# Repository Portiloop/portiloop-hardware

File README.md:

# Portiloop hardware

This repository documents hardware implementations of the `Portiloop` device. 
Which is a portable EEG closed-loop stimulation device.
[The software repository](https://github.com/Portiloop/portiloop-software) enables controlling the device from a simple Graphical User Interface (GUI).

The last hardware iteration of the `Portiloop` device consists of a PCB built around an [ADS1299 chip](https://www.ti.com/product/ADS1299) 
with connectors for a [Coral Dev Board Mini](https://coral.ai/products/dev-board-mini/#documentation).
The `ADS1299` is an ADC responsible for processing analog EEG signal.

This repository open-sources all relevant plans for building this implementation.

To view the full interactive 3D model, click below:

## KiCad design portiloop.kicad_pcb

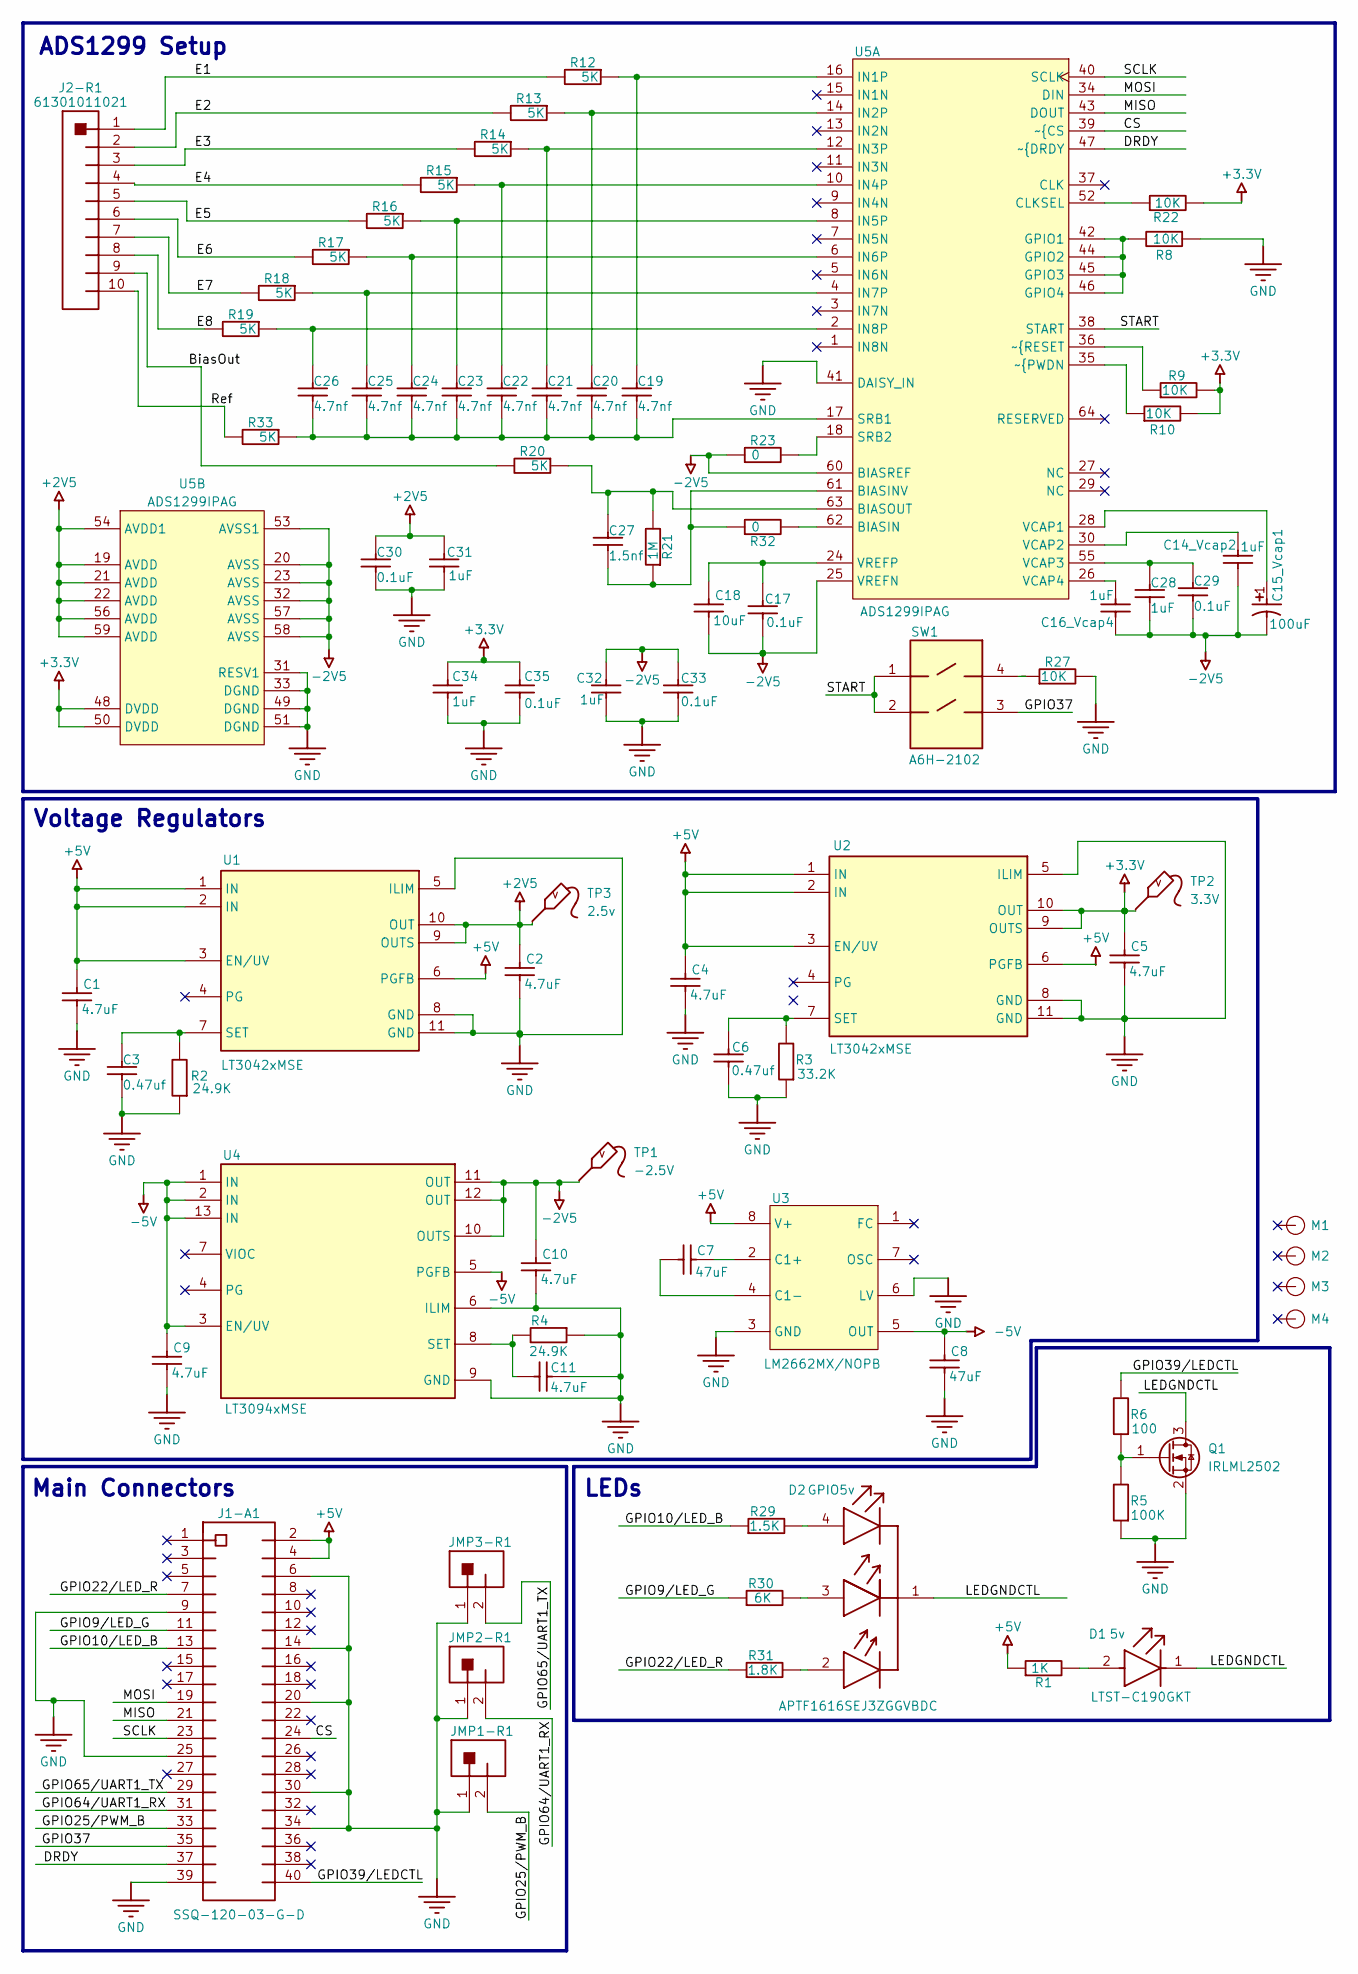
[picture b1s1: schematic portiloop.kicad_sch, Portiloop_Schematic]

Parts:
C1, C2, C4, C5, C9, C10, C11: 4.7uF; 3216[1206]_cap_3d
C3, C6: 0.47uf; 1608[0603]_cap_3d
C7, C8: 47uF; 3216[1206]_cap_3d
C14_Vcap2, C16_Vcap4, C28, C31, C32, C34: 1uF; 1608[0603]_cap_3d
C15_Vcap1: 100uF; KEMT-T491-D_M
C17, C29, C30, C33, C35: 0.1uF; 1608[0603]_cap_3d
C18: 10uF; 3216[1206]_cap_3d
C19, C20, C21, C22, C23, C24, C25, C26: 4.7nf; 1608[0603]_cap_3d
C27: 1.5nf; 1608[0603]_cap_3d
D1: LTST-C190GKT; FP-LTST-C190GKT-MFG
D2: APTF1616SEJ3ZGGVBDC; FP-APTF1616SEJ3ZGGVBDC-MFG
J1-A1: SSQ-120-03-G-D; FP-SSQ-120-03-G-D-MFG
J2-R1: 61301011021
JMP1-R1, JMP2-R1, JMP3-R1: 61300211021
M1, M2, M3, M4: board_screw
Q1: IRLML2502; SOT-23
R1: 1K; 1608[0603]_res_3d
R2, R4: 24.9K; 1608[0603]_res_3d
R3: 33.2K; 1608[0603]_res_3d
R5: 100K; 1608[0603]_res_3d
R6: 100; 1608[0603]_res_3d
R8, R22: 10k; 1608[0603]_res_3d
R9, R10, R27: 10K; 1608[0603]_res_3d
R12, R13, R14, R15, R16, R17, R18, R19, R20, R33: 5k; 1608[0603]_res_3d
R21: 1M; 1608[0603]_res_3d
R23, R32: 0; 1608[0603]_res_3d
R29: 1.5K; 1608[0603]_res_3d
R30: 6K; 1608[0603]_res_3d
R31: 1.8K; 1608[0603]_res_3d
SW1: A6H-2102; FP-A6H-2102-MFG
TP1: -2.5V; TESTPOINT
TP2: 3.3V; TESTPOINT
TP3: 2.5v; TESTPOINT
U1, U2: LT3042xMSE; FP-MSE-10-05-08-1664-IPC_C
U3: LM2662MX/NOPB; D0008A_M
U4: LT3094xMSE; FP-MSE-12-05-08-1666-IPC_A
U5: ADS1299IPAG; PAG0064A_M

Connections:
+2V5: C2.2, C30.2, C31.2, TP3.1 (T), U1.9 (OUTS), U1.10 (OUT), U5.19 (AVDD), U5.21 (AVDD), U5.22 (AVDD), U5.54 (AVDD1), U5.56 (AVDD), U5.59 (AVDD)
+3.3V: C5.2, C34.2, C35.2, R9.1, R10.1, R22.1, TP2.1 (T), U2.9 (OUTS), U2.10 (OUT), U5.48 (DVDD), U5.50 (DVDD)
+5V: C1.2, C4.2, J1-A1.2, J1-A1.4, R1.2, U1.1 (IN), U1.2 (IN), U1.3 (EN/UV), U1.6 (PGFB), U2.1 (IN), U2.2 (IN), U2.3 (EN/UV), U2.6 (PGFB), U3.8 (V+)
-2V5: C10.2, C14_Vcap2.1, C15_Vcap1.2, C16_Vcap4.1, C17.2, C18.1, C28.1, C29.1, C32.2, C33.2, R23.2, TP1.1 (T), U4.10 (OUTS), U4.11 (OUT), U4.12 (OUT), U5.20 (AVSS), U5.23 (AVSS), U5.25 (VREFN), U5.32 (AVSS), U5.53 (AVSS1), U5.57 (AVSS), U5.58 (AVSS), U5.60 (BIASREF)
-5V: C8.2, C9.2, U3.5 (OUT), U4.1 (IN), U4.2 (IN), U4.3 (EN/UV), U4.5 (PGFB), U4.13 (IN)
/BiasOut: J2-R1.9, R20.1
/CS: J1-A1.24, U5.39 (~{CS)
/DRDY: J1-A1.37, U5.47 (~{DRDY)
/E1: J2-R1.1, R12.1
/E2: J2-R1.2, R13.1
/E3: J2-R1.3, R14.1
/E4: J2-R1.4, R15.1
/E5: J2-R1.5, R16.1
/E6: J2-R1.6, R17.1
/E7: J2-R1.7, R18.1
/E8: J2-R1.8, R19.1
/GPIO9/LED_G: J1-A1.11, R30.2
/GPIO10/LED_B: J1-A1.13, R29.2
/GPIO22/LED_R: J1-A1.7, R31.2
/GPIO25/PWM_B: J1-A1.33, JMP1-R1.2
/GPIO37: J1-A1.35, SW1.3
/GPIO39/LEDCTL: J1-A1.40, R6.1
/GPIO64/UART1_RX: J1-A1.31, JMP2-R1.2
/GPIO65/UART1_TX: J1-A1.29, JMP3-R1.2
/LEDGNDCTL: D1.1 (C), D2.1 (COMMON_CATHODE), Q1.3 (D)
/MISO: J1-A1.21, U5.43 (DOUT)
/MOSI: J1-A1.19, U5.34 (DIN)
/Ref: J2-R1.10, R33.1
/SCLK: J1-A1.23, U5.40 (SCLK)
/START: SW1.1, SW1.2, U5.38 (START)
GND: C1.1, C2.1, C3.1, C4.1, C5.1, C6.2, C8.1, C9.1, C10.1, C11.1, C30.1, C31.1, C32.1, C33.1, C34.1, C35.1, J1-A1.6, J1-A1.9, J1-A1.14, J1-A1.20, J1-A1.25, J1-A1.30, J1-A1.34, J1-A1.39, JMP1-R1.1, JMP2-R1.1, JMP3-R1.1, Q1.2 (S), R2.2, R3.2, R4.2, R5.2, R8.2, R27.1, U1.5 (ILIM), U1.8 (GND), U1.11 (GND), U2.5 (ILIM), U2.8 (GND), U2.11 (GND), U3.3 (GND), U3.6 (LV), U4.6 (ILIM), U4.9 (GND), U5.31 (RESV1), U5.33 (DGND), U5.41 (DAISY_IN), U5.49 (DGND), U5.51 (DGND)
unnamed: D1.2 (A), R1.1
unnamed: D2.4 (BLUE_A), R29.1
unnamed: D2.3 (GREEN_A), R30.1
unnamed: D2.2 (RED_A), R31.1
unnamed: Q1.1 (G), R5.1, R6.2
unnamed: R27.2, SW1.4
unnamed: C3.2, R2.1, U1.7 (SET)
unnamed: C6.1, R3.1, U2.7 (SET)
unnamed: C7.2, U3.2 (C1+)
unnamed: C7.1, U3.4 (C1-)
unnamed: C11.2, R4.1, U4.8 (SET)
unnamed: R32.1, U5.62 (BIASIN)
unnamed: C27.1, R21.2, R32.2, U5.61 (BIASINV)
unnamed: C27.2, R20.2, R21.1, U5.63 (BIASOUT)
unnamed: R22.2, U5.52 (CLKSEL)
unnamed: R8.1, U5.42 (GPIO1), U5.44 (GPIO2), U5.45 (GPIO3), U5.46 (GPIO4)
unnamed: C19.2, R12.2, U5.16 (IN1P)
unnamed: C20.2, R13.2, U5.14 (IN2P)
unnamed: C21.2, R14.2, U5.12 (IN3P)
unnamed: C22.2, R15.2, U5.10 (IN4P)
unnamed: C23.2, R16.2, U5.8 (IN5P)
unnamed: C24.2, R17.2, U5.6 (IN6P)
unnamed: C25.2, R18.2, U5.4 (IN7P)
unnamed: C26.2, R19.2, U5.2 (IN8P)
unnamed: C19.1, C20.1, C21.1, C22.1, C23.1, C24.1, C25.1, C26.1, R33.2, U5.17 (SRB1)
unnamed: R23.1, U5.18 (SRB2)
unnamed: C15_Vcap1.1, U5.28 (VCAP1)
unnamed: C14_Vcap2.2, U5.30 (VCAP2)
unnamed: C28.2, C29.2, U5.55 (VCAP3)
unnamed: C16_Vcap4.2, U5.26 (VCAP4)
unnamed: C17.1, C18.2, U5.24 (VREFP)
unnamed: R10.2, U5.35 (~{PWDN)
unnamed: R9.2, U5.36 (~{RESET)

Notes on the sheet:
Voltage Regulators
ADS1299 Setup
LEDs
Main Connectors

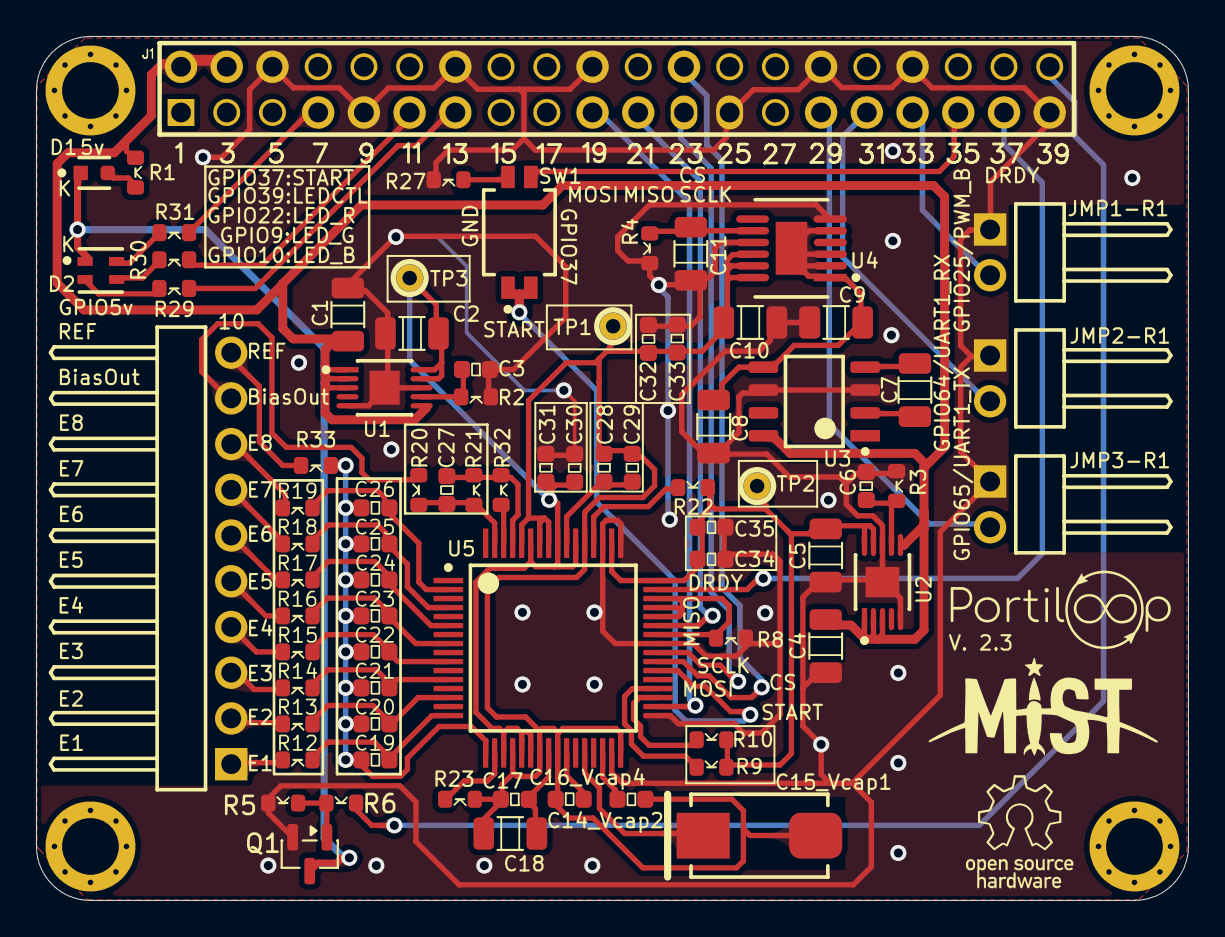
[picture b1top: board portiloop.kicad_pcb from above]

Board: 2 copper layers, 64.0 x 48.0 mm, 81 parts (1 on the bottom side), 64 nets.

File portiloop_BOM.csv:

Id,Designator,Footprint,Quantity,Designation,Part #
1,"C10,C1,C5,C4,C2,C9,C11",3216[1206]_cap,7,4.7uF,CL31B475KBHNNNE
2,C15_Vcap1,KEMT-T491-D_M,1,100uF,T491D107K016AT
3,"C16_Vcap4,C34,C31,C14_Vcap2,C32,C28",1608[0603]_cap,6,1uF,CC0603KRX5R8BB105
4,C18,3216[1206]_cap,1,10uF,CC1206KKX7R8BB106
5,"C21,C26,C22,C20,C23,C19,C25,C24",1608[0603]_cap,8,4.7nf,CC0603KRX7R9BB472
6,C27,1608[0603]_cap,1,1.5nf,CC0603KRX7R9BB152
7,"C35,C17,C33,C29,C30",1608[0603]_cap,5,0.1uF,CC0603KRX7R9BB104
8,"C6,C3",1608[0603]_cap,2,0.47uf,CC0603KRX7R9BB474
9,"C8,C7",3216[1206]_cap,2,47uF,GRM31CR60J476ME19L
10,D2,FP-APTF1616SEJ3ZGGVBDC-MFG,1,APTF1616SEJ3ZGGVBDC,
11,D1,FP-LTST-C190GKT-MFG,1,LTST-C190GKT,
12,J1-A1,FP-SSQ-120-03-G-D-MFG,1,SSQ-120-03-G-D,
13,J2-R1,61301011021,1,61301011021,
14,"JMP1-R1,JMP2-R1,JMP3-R1",61300211021,3,61300211021,
15,"M2,M4,M3,M1",board_screw,4,DNP,DNP
16,Q1,SOT-23,1,IRLML2502,IRLML2502TRPBF
17,R1,1608[0603]_res,1,1K,RC0603FR-071KL
18,"R12,R19,R33,R14,R18,R20,R16,R17,R15,R13",1608[0603]_res,10,5K OR 4.99K,RC0603FR-074K99L
19,R21,1608[0603]_res,1,1M,RC0603FR-071ML
20,R29,1608[0603]_res,1,1.5K,RC0603FR-071K5L
21,R3,1608[0603]_res,1,33.2K,RC0603FR-0733K2L
22,R30,1608[0603]_res,1,6K OR 6.04K,RC0603FR-076K04L
23,R31,1608[0603]_res,1,1.8K,RC0603FR-071K8L
24,"R32,R23",1608[0603]_res,2,0,RC0603FR-070RL
25,"R4,R2",1608[0603]_res,2,24.9K,RC0603FR-0724K9L
26,R5,1608[0603]_res,1,100K,0603SAJ0104T5E
27,R6,1608[0603]_res,1,100,RC0603JR-07100RL
28,"R8,R9,R10,R22,R27",1608[0603]_res,5,10K,RC0603FR-0710KL
29,SW1,FP-A6H-2102-MFG,1,A6H-2102,
30,"TP1,TP2,TP3",TESTPOINT,1,DNP,DNP
31,"U2,U1",FP-MSE-10-05-08-1664-IPC_C,2,LT3042xMSE,LT3042EMSE#PBF
32,U3,D0008A_M,1,LM2662MX/NOPB,LM2662MX/NOPB
33,U4,FP-MSE-12-05-08-1666-IPC_A,1,LT3094xMSE,LT3094EMSE#PBF
34,U5,PAG0064A_M,1,ADS1299IPAG,

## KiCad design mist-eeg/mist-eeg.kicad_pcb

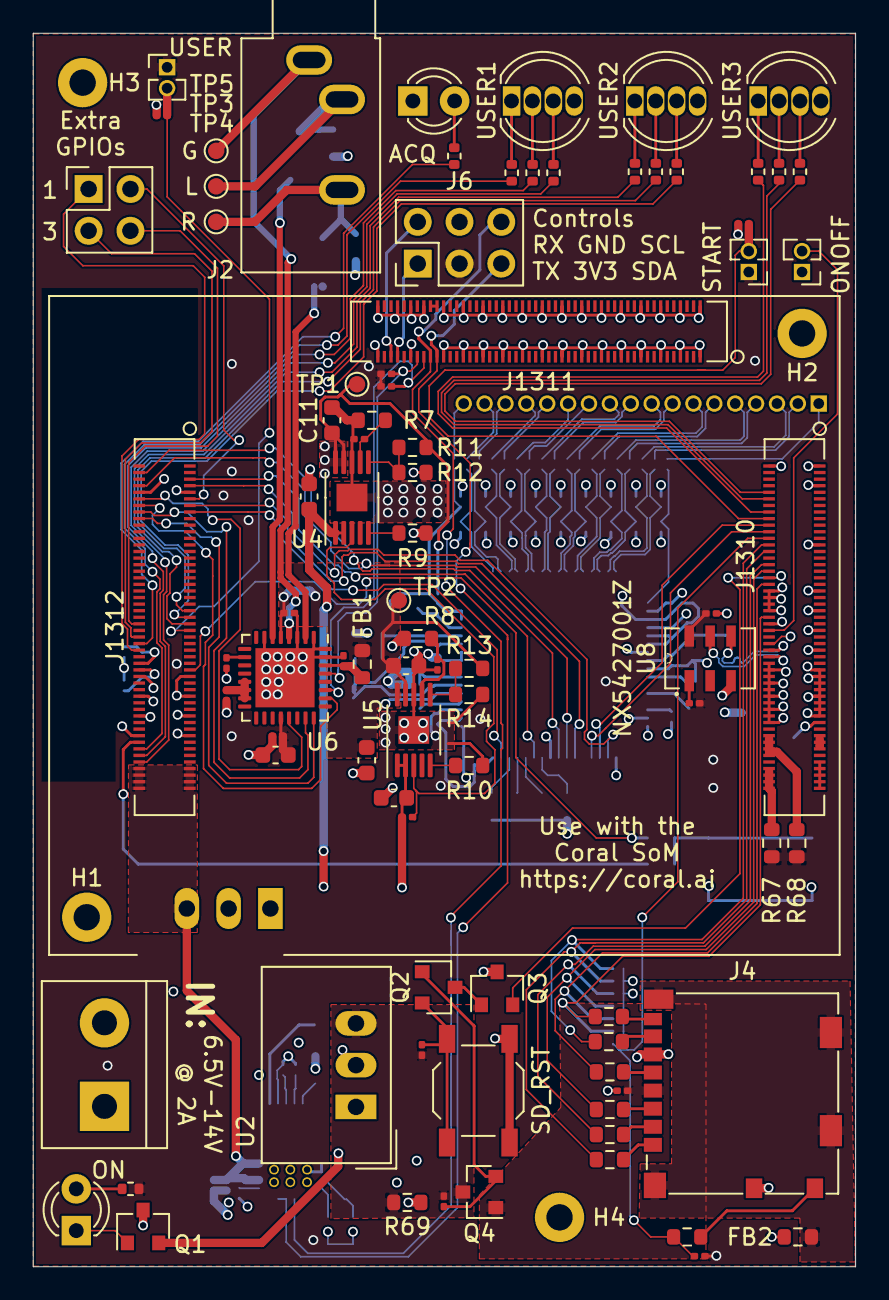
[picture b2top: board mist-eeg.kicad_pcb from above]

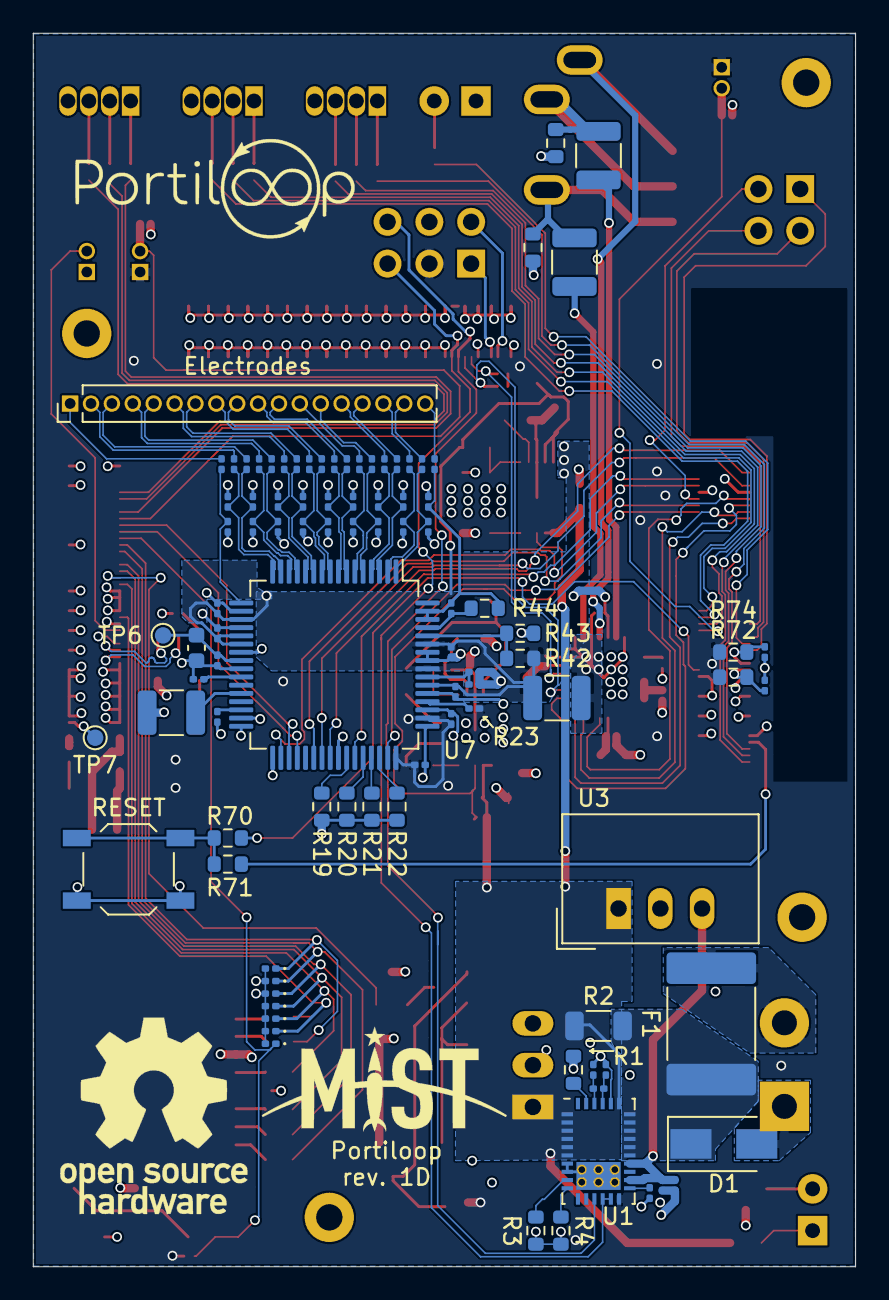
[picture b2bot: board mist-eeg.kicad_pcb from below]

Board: 4 copper layers, 50.0 x 75.0 mm, 185 parts (95 on the bottom side), 159 nets.

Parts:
C1, C2, C3, C4, C27, C28, C29, C32: 1uF; C_0201_0603Metric
C5, C6, C9, C10, C15, C16, C17, C20, C21, C22, C23, C24, C25, C30, C31, C53, C55, C56: 0u1F; C_0201_0603Metric
C7, C8, C11, C12, C18, C19, C54: 10uF; C_0603_1608Metric
C13, C14: 220uF; C_1210_3225Metric
C26, C33: 100uF; C_1210_3225Metric
C34, C35, C36, C37, C38, C39, C40, C41, C42, C43, C44, C45, C46, C47, C48, C49, C50, C51: 4n7F; C_0201_0603Metric
C52: 1n5F; C_0201_0603Metric
D1: D_TVS; D_SMA
D2: ON; LED_D3.0mm
D3: ACQ; LED_D3.0mm
D4: USER1; LED_D5.0mm-4_RGB
D5: USER3; LED_D5.0mm-4_RGB
D6: USER2; LED_D5.0mm-4_RGB
D7, D8, D9, D10, D11, D12, D13: TPD1E6B06DPLR; D_0201_0603Metric
F1: 3 A, 20 V; Fuse_2920_7451Metric
FB1, FB2: Ferrite_Bead_Small; R_0603_1608Metric
H1, H2, H3, H4: MountingHole; MountingHole_1.6mm
J1: Power_6.5V-14V; TerminalBlock_bornier-2_P5.08mm
J2: Audio; Jack_3.5mm_CUI_SJ1-3533NG_Horizontal
J3: Electrodes; PinHeader_1x18_P1.27mm_Vertical
J4: Micro_SD_Card_Det; microSD_HC_Molex_104031-0811
J5: Extra GPIOs; PinHeader_2x02_P2.54mm_Vertical
J6: Digital buses; PinHeader_2x03_P2.54mm_Vertical
J7: J1312; DF40HC3.0-100DS-0.4V58
J8: J1311; DF40HC3.0-100DS-0.4V58
J9: J1310; DF40HC3.0-100DS-0.4V58
Q1: NMOS_DGS (3V3); SOT-23
Q2, Q3: NMOS_DGS (3.3V); SOT-23
Q4: PMOS_DGS (3.3V @ 1A); SOT-23
R1, R3, R4, R9, R10, R11, R13, R58, R59, R60, R61, R62, R63, R64, R67, R70: 0R; R_0603_1608Metric
R2: DNF; R_1206_3216Metric
R5, R17, R18, R23, R55, R56, R57, R65, R66, R73, R75, R76: 4k7; R_0201_0603Metric
R6, R45, R46, R47, R48, R49, R50, R51, R52, R53, R54: 1k; R_0402_1005Metric
R7: TNPW060349K9BEEA; R_0603_1608Metric
R8: TNPW060318K0BEEA; R_0603_1608Metric
R12, R14, R15, R16, R19, R20, R21, R22: 10k; R_0603_1608Metric
R24, R25, R26, R27, R28, R29, R30, R31, R32, R33, R34, R35, R36, R37, R38, R39, R40, R41: 4k99; R_0201_0603Metric
R42, R43, R68, R69, R71, R72, R74: DNF; R_0603_1608Metric
R44: 1M; R_0603_1608Metric
SW1: START; PinHeader_1x02_P1.27mm_Vertical
SW2: USER; PinHeader_1x02_P1.27mm_Vertical
SW3: SD_RST; SW_SPST_TL3342
SW4: RESET; SW_SPST_TL3342
SW5: ONOFF; PinHeader_1x02_P1.27mm_Vertical
TP1: +5V0_ANA; TestPoint_Pad_D1.0mm
TP2: +1V8_ANA; TestPoint_Pad_D1.0mm
TP3: T; TestPoint_Pad_D1.0mm
TP4: R; TestPoint_Pad_D1.0mm
TP5: S; TestPoint_Pad_D1.0mm
TP6: VREFP; TestPoint_Pad_D1.0mm
TP7: ~POR~; TestPoint_Pad_D1.0mm
U1: LTC2947
U2: TSR_1-2433; Converter_DCDC_TRACO_TSR-1_THT
U3: TSR_2-2450; Converter_DCDC_TRACO_TSR-1_THT
U4, U5: LT3042xMSE; MSOP-10-1EP_3x3mm_P0.5mm_EP1.68x1.88mm
U6: SGTL5000XNAA3; QFN-32-1EP_5x5mm_P0.5mm_EP3.6x3.6mm
U7: ADS1299; TQFP-64_10x10mm_P0.5mm
U8: NX5427001Z

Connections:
+3V3: C17.1, C18.1, C28.1, C30.1, C56.2, J6.3, R6.1, R17.1, R18.1, R23.2, R57.1, R67.2, R68.2, R69.2, R72.2, R74.2, R76.2, SW1.1, SW2.1, U1.16, U6.20, U7.48, U7.50, U8.6
/+1V8_ANA: C12.1, C19.1, C21.1, FB1.2, R13.1, TP2.1, U5.9, U5.10, U6.5
/+3V3_SD: Q4.3, R65.1, R66.1, R69.1, U2.3
/+5V0_ANA: C11.1, C22.1, C23.1, C24.1, C25.1, C26.1, R11.1, R42.1, TP1.1, U4.9, U4.10, U7.19, U7.21, U7.22, U7.54, U7.56, U7.59
/+5V_SOM: C1.1, C2.1, J7.93, J7.94, J7.95, J7.96, J7.97, J7.98, J7.99, J7.100, U1.18, U1.20, U3.3
/AQUISITION: J7.56, R45.2
/AUDIO_BCLK: J7.18, U6.24
/AUDIO_LRCLK: J7.16, U6.23
/AUDIO_MCLK: J7.12, U6.21
/AUDIO_SCL: J8.87, R17.2, U6.29
/AUDIO_SDA: J8.85, R18.2, U6.27
/AUDIO_SDATA: J7.14, U6.26
/CTRL_SCL: J6.6, J8.83, U1.13
/CTRL_SDA: J6.5, J8.81, U1.14, U1.15
/EEG/BIASIN: C35.1, C52.2, R25.1, R44.2, U7.62, U7.63
/EEG/BIASINV: C52.1, R44.1, U7.61
/EEG/BIASREF: R42.2, R43.1, U7.60
/EEG/BIAS_ELEC_O: J3.18, R25.2
/EEG/IN1N: C37.2, R27.1, U7.15
/EEG/IN1P: C36.1, R26.1, U7.16
/EEG/IN1_ON: J3.3, R27.2
/EEG/IN1_OP: J3.2, R26.2
/EEG/IN2N: C39.2, R29.1, U7.13
/EEG/IN2P: C38.1, R28.1, U7.14
/EEG/IN2_ON: J3.5, R29.2
/EEG/IN2_OP: J3.4, R28.2
/EEG/IN3N: C41.2, R31.1, U7.11
/EEG/IN3P: C40.1, R30.1, U7.12
/EEG/IN3_ON: J3.7, R31.2
/EEG/IN3_OP: J3.6, R30.2
/EEG/IN4N: C43.2, R33.1, U7.9
/EEG/IN4P: C42.1, R32.1, U7.10
/EEG/IN4_ON: J3.9, R33.2
/EEG/IN4_OP: J3.8, R32.2
/EEG/IN5N: C45.2, R35.1, U7.7
/EEG/IN5P: C44.1, R34.1, U7.8
/EEG/IN5_ON: J3.11, R35.2
/EEG/IN5_OP: J3.10, R34.2
/EEG/IN6N: C47.2, R37.1, U7.5
/EEG/IN6P: C46.1, R36.1, U7.6
/EEG/IN6_ON: J3.13, R37.2
/EEG/IN6_OP: J3.12, R36.2
/EEG/IN7N: C49.2, R39.1, U7.3
/EEG/IN7P: C48.1, R38.1, U7.4
/EEG/IN7_ON: J3.15, R39.2
/EEG/IN7_OP: J3.14, R38.2
/EEG/IN8N: C51.2, R41.1, U7.1
/EEG/IN8P: C50.1, R40.1, U7.2
/EEG/IN8_ON: J3.17, R41.2
/EEG/IN8_OP: J3.16, R40.2
/EEG/REF_ELEC: C34.1, R24.1, U7.17
/EEG/REF_ELEC_O: J3.1, R24.2
/EEG/VREFP: C53.1, C54.1, TP6.1, U7.24
/EEG_MISO: J7.5, U7.43
/EEG_MOSI: J7.7, U7.34
/EEG_SCK: J7.4, U7.40
/EEG_START: J7.13, U7.38
/SD_CLK: D12.1, J9.48, R63.2
/SD_CMD: D11.1, J9.26, R62.2
/SD_DAT0: D7.1, J9.28, R58.2
/SD_DAT1: D8.1, J9.32, R59.2
/SD_DAT2: D9.1, J9.34, R60.2
/SD_DAT3: D10.1, J9.38, R61.2
/SD_DATA/+PWR: C55.1, J4.4, Q4.1
/START: J9.18, R55.1, SW1.2
/SoM/BOOT_MODE0: J7.64, R72.1, R73.2
/SoM/BOOT_MODE1: J7.62, R74.1, R75.2
/SoM/CLK+: J9.58, U8.4
/SoM/CLK-: J9.60, U8.5
/SoM/DCDC_3V3: J9.84, J9.86, J9.88, J9.90, R68.1
/SoM/EXTRA_1: J5.1, J7.58
/SoM/EXTRA_2: J5.2, J7.11
/SoM/EXTRA_3: J5.3, J7.54
/SoM/EXTRA_4: J5.4, J7.50
/SoM/NVCC_ENET_2V5: J9.83, J9.85, J9.87
/SoM/ONOFF: J9.52, SW5.2
/SoM/RXD: J6.2, J8.95
/SoM/TXD: J6.1, J8.93
/SoM/USB1_VBUS: J8.82, J8.84
/SoM/VDDA_1V8: J9.91, J9.93, J9.95, J9.97, J9.99
/SoM/VDD_3V3: J9.94, J9.96, J9.98, J9.100, R67.1
/SoM/~POR~: J9.79, TP7.1
/SoM/~PWR_ON~: J7.86, R71.1
/SoM/~RESET~: J7.63, R70.1
/USER: J7.51, R56.1, SW2.2
/USER1_B: J7.92, R48.2
/USER1_G: J7.90, R47.2
/USER1_R: J7.88, R46.2
/USER2_B: J7.47, R54.2
/USER2_G: J7.45, R53.2
/USER2_R: J7.49, R52.2
/USER3_B: J9.10, R51.2
/USER3_G: J9.12, R50.2
/USER3_R: J9.16, R49.2
/audio/CM: C15.1, U6.13, U6.14, U6.15
/audio/DVDD: C20.1, FB1.1, U6.30
/audio/HPGND: J2.S, TP5.1, U6.4
/audio/LEFT: C13.1, U6.6
/audio/R: C14.2, J2.R, R16.1, TP4.1
/audio/RIGHT: C14.1, U6.2
/audio/T: C13.2, J2.T, R15.1, TP3.1
/power/+PWR: C7.1, C8.1, Q1.2, R2.1, R5.2, U1.1, U1.2, U1.3, U1.4, U1.5, U1.6, U1.27, U2.1, U3.1, U4.1, U4.2, U5.1, U5.2
/power/+PWR_IN: D1.1, F1.1, R2.2, U1.21, U1.22, U1.23, U1.24, U1.25, U1.26
/power/AD0: R3.1, U1.9
/power/AD1: R4.1, U1.10
/power/audio-power/ENA: R5.1, U4.3, U5.3
/power/audio-power/LIM_1V8: R10.1, U5.5
/power/audio-power/LIM_5V0: R9.1, U4.5
/power/audio-power/PGFB_1V8: R13.2, R14.1, U5.6
/power/audio-power/PGFB_5V0: R11.2, R12.1, U4.6
/power/audio-power/SET_1V8: C10.1, R8.1, U5.7
/power/audio-power/SET_5V0: C9.1, R7.1, U4.7
/~EEG_CS~: J7.8, U7.39
/~EEG_DRDY~: J7.15, U7.47
/~EEG_PWDN~: J9.20, U7.35
/~EEG_RESET~: J9.22, U7.36
/~SD_CONNECTED~: D13.1, J9.24, R57.2, R64.2
/~SD_RST~: J9.36, Q3.2
GND: C1.2, C2.2, C3.1, C5.1, C6.1, C7.2, C8.2, C9.2, C10.2, C11.2, C12.2, C15.2, C16.2, C17.2, C18.2, C19.2, C20.2, C21.2, C22.2, C23.2, C24.2, C25.2, C26.2, C27.1, C28.2, C29.1, C30.2, C31.1, C32.1, C33.1, C34.2, C35.2, C36.2, C37.1, C38.2, C39.1, C40.2, C41.1, C42.2, C43.1, C44.2, C45.1, C46.2, C47.1, C48.2, C49.1, C50.2, C51.1, C53.2, C54.2, C55.2, C56.1, D1.2, D3.1, D4.4, D5.4, D6.4, D7.2, D8.2, D9.2, D10.2, D11.2, D12.2, D13.2, FB2.1, J1.1, J4.6, J4.9, J6.4, J7.9, J7.10, J7.65, J7.66, J7.71, J7.72, J7.77, J7.78, J7.83, J7.84, J8.1, J8.2, J8.7, J8.8, J8.13, J8.14, J8.19, J8.20, J8.25, J8.26, J8.31, J8.32, J8.37, J8.38, J8.43, J8.44, J8.49, J8.50, J8.55, J8.56, J8.61, J8.62, J8.67, J8.68, J8.73, J8.74, J8.79, J8.80, J8.86, J8.89, J8.90, J8.94, J8.99, J8.100, J9.1, J9.2, J9.7, J9.25, J9.39, J9.40, J9.42, J9.44, J9.45, J9.46, J9.50, J9.51, J9.56, J9.57, J9.62, J9.63, J9.64, J9.65, J9.66, J9.67, J9.68, J9.69, J9.70, J9.71, J9.72, J9.73, J9.74, J9.75, J9.76, J9.77, J9.78, J9.80, Q1.3, Q3.3, R1.2, R3.2, R4.2, R7.2, R8.2, R9.2, R10.2, R12.2, R14.2, R15.2, R16.2, R19.1, R20.1, R21.1, R22.1, R43.2, R55.2, R56.2, R73.1, R75.1, SW3.1, SW4.1, SW5.1, U1.7, U1.8, U1.28, U1.33, U2.2, U3.2, U4.8, U4.11, U5.8, U5.11, U6.1, U6.3, U6.7, U6.31, U6.32, U6.33, U7.18, U7.20, U7.23, U7.25, U7.31, U7.32, U7.33, U7.41, U7.49, U7.51, U7.53, U7.57, U7.58, U8.3
unnamed: C3.2, U1.17
unnamed: C4.1, C5.2, U1.29
unnamed: C4.2, C6.2, U1.30
unnamed: C16.1, U6.10
unnamed: C27.2, U7.26
unnamed: C29.2, C31.2, U7.55
unnamed: C32.2, U7.30
unnamed: C33.2, U7.28
unnamed: D2.1, Q1.1
unnamed: D2.2, R6.2
unnamed: D3.2, R45.1
unnamed: D4.1, R46.1
unnamed: D4.2, R47.1
unnamed: D4.3, R48.1
unnamed: D5.1, R49.1
unnamed: D5.2, R50.1
unnamed: D5.3, R51.1
unnamed: D6.1, R52.1
unnamed: D6.2, R53.1
unnamed: D6.3, R54.1
unnamed: F1.2, J1.2
unnamed: FB2.2, J4.11
unnamed: J4.1, R58.1
unnamed: J4.2, R59.1
unnamed: J4.3, R60.1
unnamed: J4.5, R61.1
unnamed: J4.7, R62.1
unnamed: J4.8, R63.1
unnamed: J4.10, R64.1
unnamed: Q2.1, Q4.2, R66.2
unnamed: Q2.2, R65.2, SW3.2
unnamed: Q2.3, Q3.1
unnamed: R1.1, U1.31
unnamed: R19.2, U7.42
unnamed: R20.2, U7.44
unnamed: R21.2, U7.45
unnamed: R22.2, U7.46
unnamed: R23.1, U7.52
unnamed: R70.2, R71.2, SW4.2
unnamed: R76.1, U8.1

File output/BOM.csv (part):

Id,Quantity,Reference Part Designator,Manufacturer,Designation,Description,Package,Type,Do Not Fit,Digikey choice #1,Digikey choice #2,Digikey choice #3,Mouser choice #1,Mouser choice #2,Mouser choice #3,Notes,Unit Price (est.),Total price (est.),,Total price (est.),"148,43"
1,8,"C1,C2,C3,C4,C27,C28,C29,C32",,,1uF,C_0201_0603Metric,SMD,,https://www.digikey.com/en/products/detail/samsung-electro-m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,,,https://www.mouser.com/ProductDetail/Samsung-Electro-Mechani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,https://www.mouser.com/ProductDetail/Murata-Electronics/GRM0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,,±10%,"0,3","2,4",,Unique parts,35
2,18,"C5,C6,C9,C10,C15,C16,C17,C20,C21,C22,C23,C24,C25,C30,C31,C53,C55,C56",,,0u1F,C_0201_0603Metric,SMD,,https://www.digikey.com/en/products/detail/murata-electronic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,https://www.digikey.com/en/products/detail/murata-electronic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,https://www.digikey.com/en/products/detail/walsin-technology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,https://www.mouser.com/ProductDetail/Murata-Electronics/GRM0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,https://www.mouser.com/ProductDetail/Murata-Electronics/GRM0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,https://www.mouser.com/ProductDetail/TDK/C0603X5R1E104K030BB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,±10%,"0,06","1,08",,Pads,733
3,7,"C7,C8,C11,C12,C18,C19,C54",,,10uF,C_0603_1608Metric,SMD,,https://www.digikey.com/en/products/detail/murata-electronic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,https://www.digikey.com/en/products/detail/murata-electronic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,https://www.digikey.com/en/products/detail/tdk-corporation/C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,https://www.mouser.com/ProductDetail/Murata-Electronics/GRM1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,https://www.mouser.com/ProductDetail/Murata-Electronics/GRT1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,https://www.mouser.com/ProductDetail/TDK/C1608X5R1C106M080AB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,±10%,"0,5","3,5",,SMD parts,151
4,2,"C13,C14",,,220uF,C_1210_3225Metric,SMD,,https://www.digikey.com/en/products/detail/murata-electronic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,https://www.digikey.com/en/products/detail/taiyo-yuden/JMK32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,,https://www.mouser.com/ProductDetail/Murata-Electronics/GRM3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,https://www.mouser.com/ProductDetail/Taiyo-Yuden/JMK325ABJ22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,,±20%,2,4,,,
5,2,"C26,C33",,,100uF,C_1210_3225Metric,SMD,,https://www.digikey.com/en/products/detail/taiyo-yuden/EMK32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,,,https://www.mouser.com/ProductDetail/AVX/1210YD107MAT2A?qs=d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,,,±20%,2,4,,,
6,18,"C34,C35,C36,C37,C38,C39,C40,41,42,C43,C44,C45,C46,C47,C48,C49,C50,C51",,,4n7F,C_0201_0603Metric,SMD,,https://www.digikey.com/en/products/detail/murata-electronic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,https://www.digikey.com/en/products/detail/murata-electronic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,https://www.digikey.com/en/products/detail/tdk-corporation/C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,https://www.mouser.com/ProductDetail/Murata-Electronics/GRM0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,https://www.mouser.com/ProductDetail/Murata-Electronics/GRM0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,https://www.mouser.com/ProductDetail/AVX/02013C472KAT2A?qs=%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,±10%,"0,1","1,8",,,
7,1,C52,,,1n5F,C_0201_0603Metric,SMD,,https://www.digikey.com/en/products/detail/murata-electronic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,https://www.digikey.com/en/products/detail/murata-electronic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,https://www.digikey.com/en/products/detail/yageo/CC0201KRX7R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,https://www.mouser.com/ProductDetail/Murata-Electronics/GRM0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,https://www.mouser.com/ProductDetail/Murata-Electronics/GRM0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,https://www.mouser.com/ProductDetail/Murata-Electronics/GRM0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,±10%,"0,1","0,1",,,
8,1,D1,,,Power TVS,D_SMA,SMD,,https://www.digikey.com/en/products/detail/vishay-general-se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,https://www.digikey.com/en/products/detail/vishay-general-se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,,https://www.mouser.com/ProductDetail/Vishay-General-Semicond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,https://www.mouser.com/ProductDetail/Microchip-Technology/SM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,,,"0,4","0,4",,,
9,2,"D2,D3",,,Status LEDs,LED_D3.0mm,TH,,https://www.digikey.com/en/products/detail/w%C3%BCrth-elektr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,https://www.digikey.com/en/products/detail/w%C3%BCrth-elektr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,,https://www.mouser.com/ProductDetail/Wurth-Elektronik/151031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,,,,"0,17","0,34",,,
10,3,"D4,D5,D6",,,User LEDs,LED_D5.0mm-4_RGB,TH,,https://www.digikey.com/en/products/detail/inolux/HV-5RGB60/7604616,,,https://www.mouser.com/ProductDetail/Inolux/HV-5RGB60?qs=qSf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,,,,1,3,,,
11,7,"D13,D12,D11,D10,D9,D8,D7",,TPD1E6B06DPLR,SD TVS,D_0201_0603Metric,SMD,,https://www.digikey.com/en/products/detail/texas-instruments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,https://www.digikey.com/en/products/detail/texas-instruments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,,https://www.mouser.com/ProductDetail/Texas-Instruments/TPD1E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,,,,"0,7","4,9",,,
12,1,F1,,,"Power fuse (3A, 20V)",Fuse_2920_7451Metric,SMD,,https://www.digikey.com/en/products/detail/bel-fuse-inc/0ZCF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,,,https://www.mouser.com/ProductDetail/Bel-Fuse/0ZCF0200AF2C?q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,,,,"0,2","0,2",,,
13,2,"FB1,FB2",,,Shield decoupling,R_0603_1608Metric,SMD,,https://www.digikey.com/en/products/detail/laird-signal-inte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,https://www.digikey.com/en/products/detail/murata-electronic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,https://www.digikey.com/en/products/detail/w%C3%BCrth-elektr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,https://www.mouser.com/ProductDetail/Murata-Electronics/BLM1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,https://www.mouser.com/ProductDetail/Murata-Electronics/BLM1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,https://www.mouser.com/ProductDetail/Murata-Electronics/BLM1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,,"0,1","0,2",,,
14,2,"H2,H1",,,Mounting Holes,MountingHole_1.6mm,–,x,,,,,,,,,,,,
15,1,J1,,,Power connector,TerminalBlock_bornier-2_P5.08mm,TH,,https://www.digikey.com/en/products/detail/cui-devices/TB007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,https://www.digikey.com/en/products/detail/cui-devices/TB004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,https://www.digikey.com/en/products/detail/weidm%C3%BCller/1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,https://www.mouser.com/ProductDetail/CUI-Devices/TB007-508-0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,https://www.mouser.com/ProductDetail/CUI-Devices/TB004-508-0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,,,"0,8","0,8",,,
16,1,J2,,,Audio,Jack_3.5mm_CUI_SJ1-3533NG_Horizontal,TH,,https://www.digikey.com/en/products/detail/cui-devices/SJ1-3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,,,https://www.mouser.com/ProductDetail/CUI-Devices/SJ1-3533NG?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,,,,"1,2","1,2",,,
17,1,J3,,,Electrodes,PinHeader_1x18_P1.27mm_Vertical,–,x,,,,,,,,,,,,
18,1,J4,,,Molex 104031,microSD_HC_Molex_104031-0811,SMD,,https://www.digikey.com/en/products/detail/molex/1040310811/2370379,,,https://www.mouser.com/ProductDetail/Molex/104031-0811?qs=%2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,,,,2,2,,,
19,1,J5,,,Extra GPIOs,PinHeader_2x02_P2.54mm_Vertical,–,x,,,,,,,,,,,,
20,1,J6,,,Digital buses,PinHeader_2x03_P2.54mm_Vertical,–,x,,,,,,,,,,,,
21,3,"J7,J8,J9",,"J1310,J1311,J1312",SoM headers,DF40HC3.0-100DS-0.4V58,SMD,,,,,https://www.mouser.com/ProductDetail/Hirose-Connector/DF40HC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,,,,"2,6","7,8",,,
22,3,"Q1,Q2,Q3",,NMOS_DGS (3.3V),Logic mosfets,SOT-23,SMD,,https://www.digikey.com/en/products/detail/diodes-incorporat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,https://www.digikey.com/en/products/detail/stmicroelectronic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,https://www.digikey.com/en/products/detail/taiwan-semiconduc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,https://www.mouser.com/ProductDetail/Vishay-Siliconix/SI2302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,https://www.mouser.com/ProductDetail/Diodes-Incorporated/DMN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,https://www.mouser.com/ProductDetail/Nexperia/NX138AKR?qs=1f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,,"0,5","1,5",,,
23,1,Q4,,PMOS_DGS (3.3V @ 1A),Power mosfet,SOT-23,SMD,,https://www.digikey.com/en/products/detail/vishay-siliconix/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,https://www.digikey.com/en/products/detail/vishay-siliconix/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,https://www.digikey.com/en/products/detail/vishay-siliconix/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,https://www.mouser.com/ProductDetail/Vishay-Siliconix/SI2319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,https://www.mouser.com/ProductDetail/Vishay-Siliconix/SI2315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,https://www.mouser.com/ProductDetail/Vishay-Semiconductors/S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,,"0,5","0,5",,,
24,16,"R1,R3,R4,R9,R10,R11,R13,R58,R59,R60,R61,R62,R63,R64,R67,R70",,,0R,R_0603_1608Metric,SMD,,https://www.digikey.com/en/products/detail/vishay-dale/RCS06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,https://www.digikey.com/en/products/detail/vishay-dale/CRCW0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,https://www.digikey.com/en/products/detail/yageo/RC0603JR-07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,https://www.mouser.com/ProductDetail/YAGEO/AC0603FR-070RL?qs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,https://www.mouser.com/ProductDetail/YAGEO/RC0603FR-070RL?qs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,https://www.mouser.com/ProductDetail/YAGEO/RC0603FR-100RL?qs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,±1%,"0,01","0,16",,,
25,1,R2,,,0R,R_1206_3216Metric,SMD,,https://www.digikey.com/en/products/detail/vishay-dale/CRCW1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,https://www.digikey.com/en/products/detail/vishay-dale/RCS12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,https://www.digikey.com/en/products/detail/stackpole-electro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,https://www.mouser.com/ProductDetail/Vishay-Dale/CRCW1206000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,https://www.mouser.com/ProductDetail/Vishay-Dale/RCS12060000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,https://www.mouser.com/ProductDetail/YAGEO/RC1206JR-7W0RL?qs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,±1%,"0,01","0,01",,,
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
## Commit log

2021-07-21 Initial commit :rocket:
2021-07-22 Hooked-up the SoM
2021-07-26 Finish schematic and create interface specifications
2021-07-27 Place components
2021-07-28 Advance routing
2021-07-29 Finished layout
2021-07-29 Fix text size in silkscreen
2021-07-29 Finish silkscreen
2021-07-30 Validation & fabrication layer
2021-07-30 Cleanup
2021-08-02 Update footprints based upon piece availability & generate manufacturing files
2021-08-02 Small fix to the TPS63070 footprint
2021-08-03 Update output files for PCBWay
2021-08-05 Change buckboost regulator used
2021-08-05 Switch to POL switching regulator to accelerate production of the board
2021-08-05 Add BoM
2021-08-06 Switch to bigger min via size
2021-08-06 Fix drill size for LTC2947 vias
2021-08-30 Add U8 & connectors to BOM
2021-11-25 cleaning repo
2022-02-24 readme
2022-02-24 preparing for transfer
2022-02-24 gitignore
2022-02-24 transfer FPGA complete
2022-06-02 Added case 3D file
2023-02-24 Added portiloop V2 files
2023-07-28 Upload V2.2
2023-08-30 cleanup v1
2023-08-30 Upload V2 figures
2023-08-30 v2.2
2025-12-10 version v2.3 KiCad 9.0.6
2025-12-12 STL file added
2025-12-12 STL file added to README
2025-12-12 STL file updated
2025-12-18 box added
2025-12-23 Restructure project directories

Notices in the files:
parts and their libraries:
Copyright 2021 Accelerated Designs. All rights reserved.
